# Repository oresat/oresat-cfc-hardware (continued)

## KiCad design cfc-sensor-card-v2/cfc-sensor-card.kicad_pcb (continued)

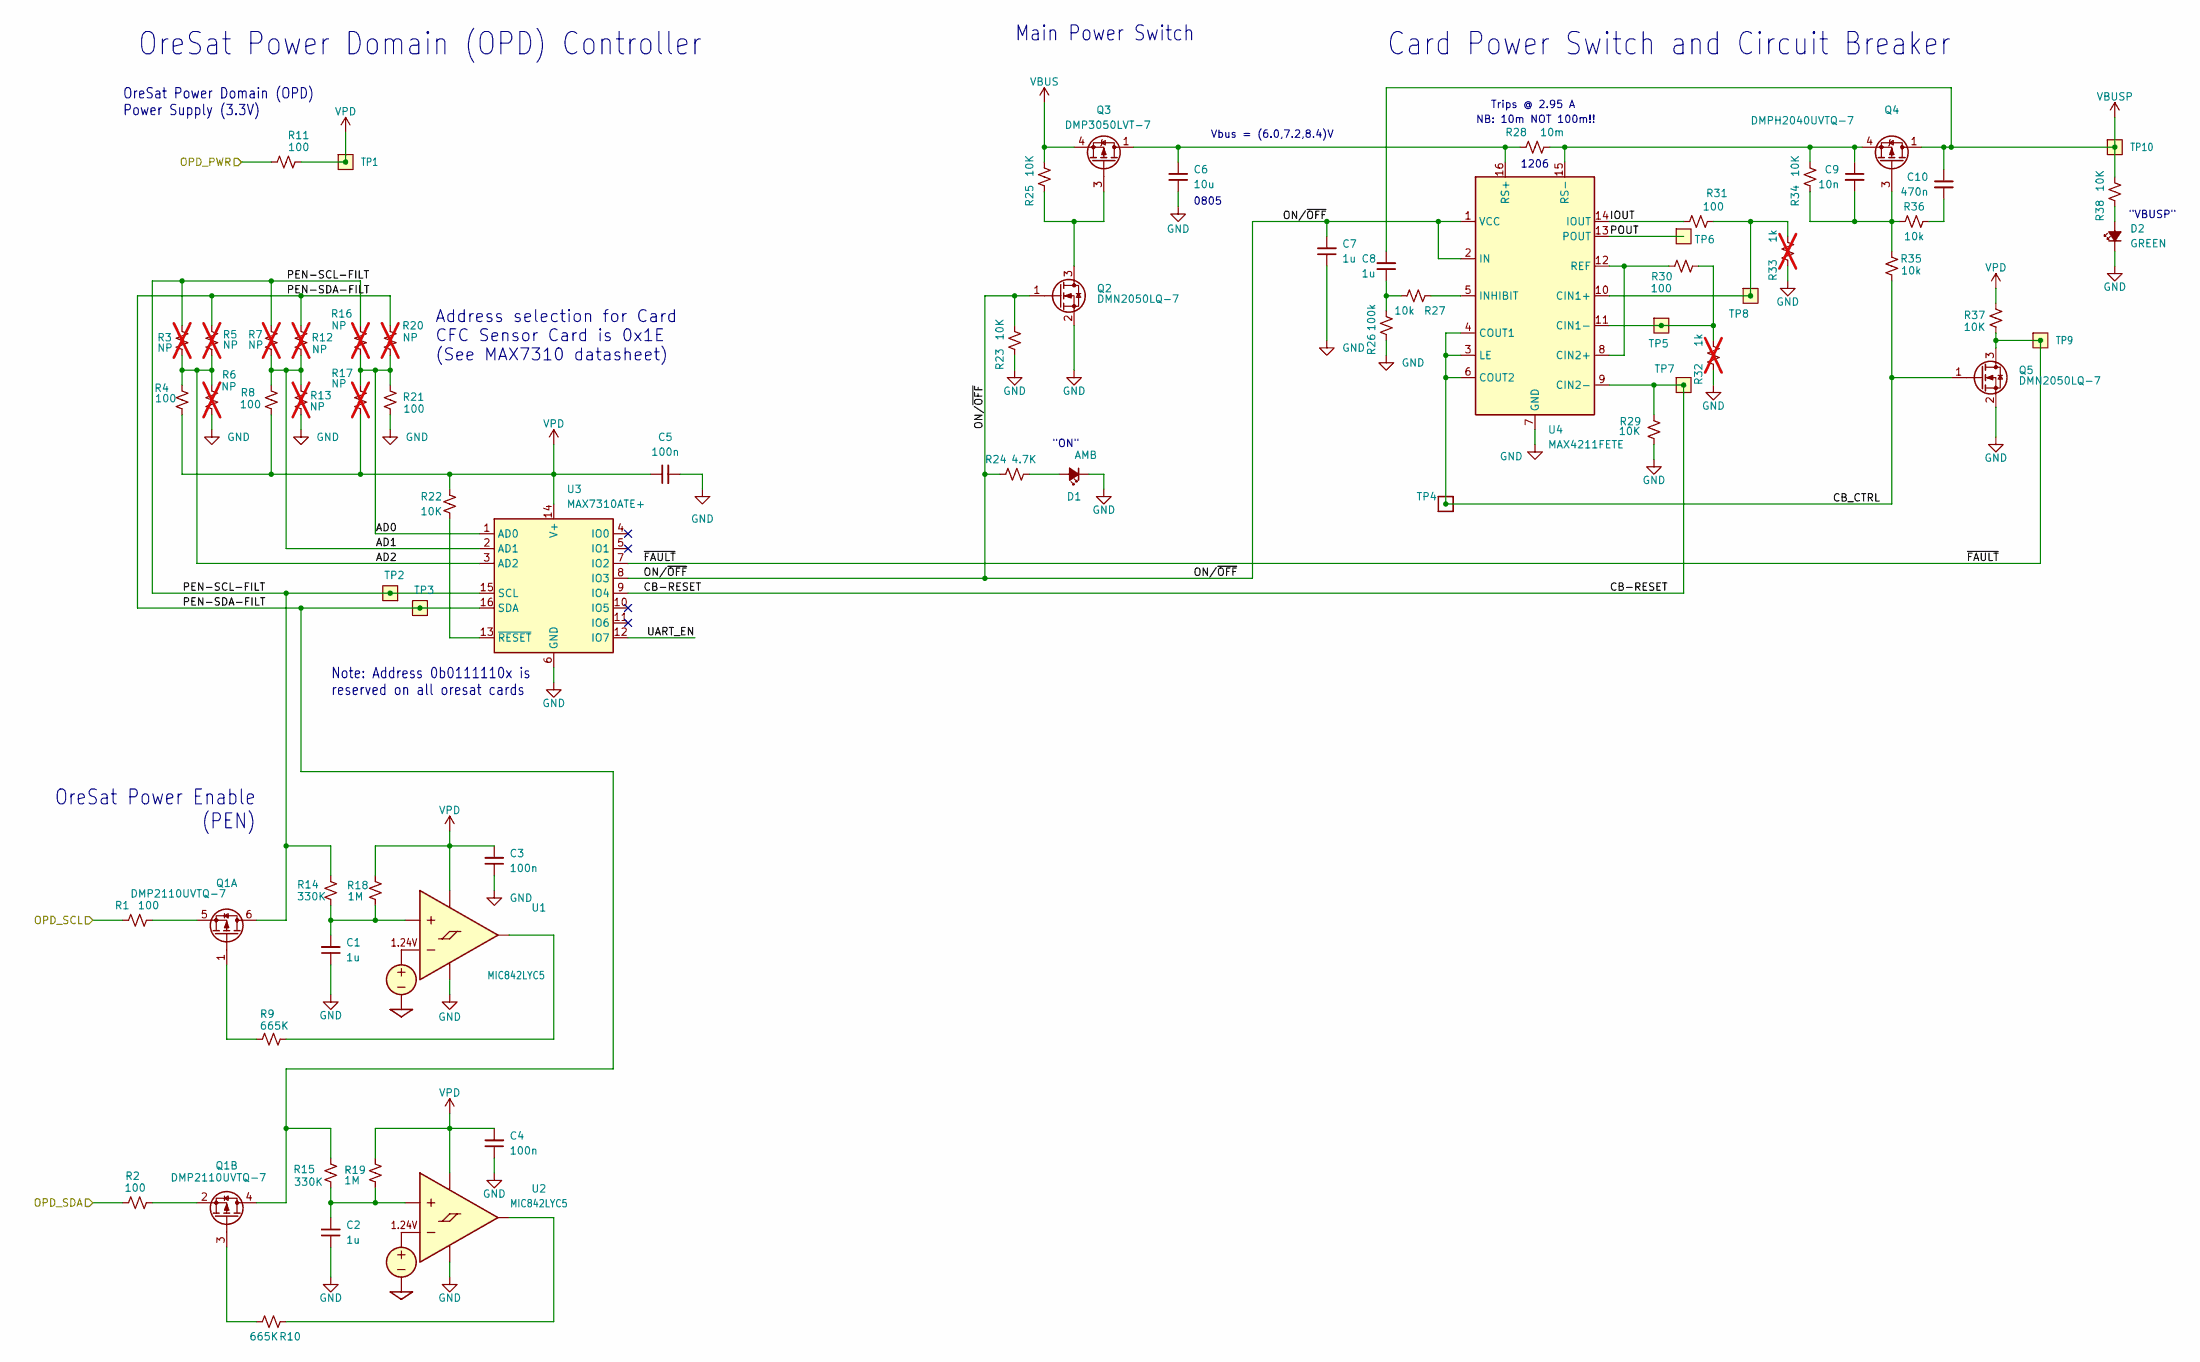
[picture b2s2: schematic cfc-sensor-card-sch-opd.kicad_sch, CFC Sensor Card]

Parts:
C1, C2, C7, C8: 1u; 0603-C-NOSILK; MPN TMK107BJ105KAHT
C3, C4, C5: 100n; 0603-C-NOSILK; MPN TMK107BJ104KAHT
C6: 10u; 0805-C-NOSILK; MPN GRT21BC71E106KE13L
C9: 10n; 0603-C-NOSILK; MPN C0603C103J5RACAUTO
C10: 470n; 0603-C-NOSILK; MPN C0603C474K3RACAUTO
D1: AMB; LED_0603_1608Metric; MPN 150060AS75000
D2: GREEN; LED_0603_1608Metric; MPN 150060GS75000
Q1: DMP2110UVTQ-7; SOT-23-6; MPN DMP2110UVTQ-7
Q2, Q5: DMN2050LQ-7; SOT-23; MPN DMN2050LQ-7
Q3: DMP3050LVT-7; TSOT-23-6; MPN DMP3050LVT-7
Q4: DMPH2040UVTQ-7; TSOT-23-6; MPN DMPH2040UVTQ-7
R1, R2, R4, R8, R11, R21, R30, R31: 100; 0603-C-NOSILK; MPN RMCF0603FT100R
R3, R5, R6, R7, R12, R13, R16, R17, R20: NP; 0603-C-NOSILK; not fitted
R9, R10: 665K; 0603-C-NOSILK; MPN RMCF0603FT665K
R14, R15: 330K; 0603-C-NOSILK; MPN RMCF0603FT330K
R18, R19: 1M; 0603-C-NOSILK; MPN RMCF0603FG1M00
R22, R23, R25, R29, R34, R37, R38: 10K; 0603-C-NOSILK; MPN RMCF0603FT10K0
R24: 4.7K; 0603-C-NOSILK; MPN RMCF0603FT4K70
R26: 100k; 0603-C-NOSILK; MPN RMCF0603FT100K
R27, R35, R36: 10k; 0603-C-NOSILK; MPN RMCF0603FT10K0
R28: 10m; R_1206_3216Metric; MPN CSRF1206FT10L0
R32, R33: 1k; 0603-C-NOSILK; not fitted
TP1, TP9, TP10: Test-Point; TestPoint-0.75mm-th
TP2, TP3, TP5, TP6, TP7, TP8: TEST-POINT; TestPoint-0.75mm-th
TP4: TestPoint-MinTH; TestPoint_Pad_D1.0mm
U1, U2: MIC842LYC5; SOT-353_SC-70-5; MPN MIC842LYC5-TR
U3: MAX7310ATE+; QFN-16-1EP_4x4mm_P0.65mm_EP2.1x2.1mm; MPN MAX7310ATE+
U4: MAX4211FETE; QFN-16-1EP_4x4mm_P0.65mm_EP2.1x2.1mm; MPN MAX4211FETE

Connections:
/OPD/AD0: R16.2, R17.1, R20.2, R21.1, U3.1 (AD0)
/OPD/AD1: R7.2, R8.1, R12.2, R13.1, U3.2 (AD1)
/OPD/AD2: R3.2, R4.1, R5.2, R6.1, U3.3 (AD2)
/OPD/CB-RESET: R29.2, TP7.1 (1_1), U3.9 (IO4), U4.9 (CIN2-)
/OPD/CB_CTRL: Q5.1 (G), R35.2, TP4.1 (1_1), U4.3 (LE), U4.4 (COUT1), U4.6 (COUT2)
/OPD/IOUT: R31.1, U4.14 (IOUT)
/OPD/ON/~OFF: C7.2, Q2.1 (G), R23.2, R24.1, U3.8 (IO3), U4.1 (VCC), U4.2 (IN)
/OPD/OPD_PWR: R11.1; also elsewhere on the board
/OPD/OPD_SCL: R1.1; also elsewhere on the board
/OPD/OPD_SDA: R2.1; also elsewhere on the board
/OPD/PEN-SCL-FILT: Q1.6 (D), R3.1, R7.1, R14.2, R16.1, TP2.1 (1_1), U3.15 (SCL)
/OPD/PEN-SDA-FILT: Q1.4 (D), R5.1, R12.1, R15.2, R20.1, TP3.1 (1_1), U3.16 (SDA)
/OPD/POUT: TP6.1 (1_1), U4.13 (POUT)
/OPD/UART_EN: U3.12 (IO7)
/OPD/~FAULT: Q5.3 (D), R37.1, TP9.1 (1_1), U3.7 (IO2)
unnamed: C8.1, R26.2, R27.2
unnamed: C10.2, R36.2
unnamed: D1.2 (A), R24.2
unnamed: D2.2 (A), R38.1
unnamed: Q1.1 (G), R9.2
unnamed: Q1.5 (S), R1.2
unnamed: Q1.3 (G), R10.2
unnamed: Q1.2 (S), R2.2
unnamed: Q2.3 (D), Q3.3 (G), R25.1
unnamed: C9.2, Q4.3 (G), R34.1, R35.1, R36.1
unnamed: C9.1, Q4.4 (S), R28.2, R34.2, U4.15 (RS-)
unnamed: C1.2, R14.1, R18.1, U1.1 (INP)
unnamed: R9.1, U1.4 (OUT)
unnamed: C2.2, R15.1, R19.1, U2.1 (INP)
unnamed: R10.1, U2.4 (OUT)
unnamed: R22.2, U3.13 (~RESET)
unnamed: R31.2, R33.2, TP8.1 (1_1), U4.10 (CIN1+)
unnamed: R30.2, R32.2, TP5.1 (1_1), U4.11 (CIN1-)
unnamed: R30.1, U4.8 (CIN2+), U4.12 (REF)
unnamed: R27.1, U4.5 (INHIBIT)
unnamed: C6.2, Q3.1 (D), Q3.2 (D), Q3.5 (D), Q3.6 (D), R28.1, U4.16 (RS+)
VBUS: Q3.4 (S), R25.2; also elsewhere on the board
VBUSP: C8.2, C10.1, Q4.1 (D), Q4.2 (D), Q4.5 (D), Q4.6 (D), R38.2, TP10.1 (1_1); also elsewhere on the board
VPD: C3.2, C4.2, C5.1, R4.2, R8.2, R11.2, R17.2, R18.2, R19.2, R22.1, R37.2, TP1.1 (1_1), U1.5 (VDD), U2.5 (VDD), U3.14 (V+)

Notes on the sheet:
Trips @ 2.95 A
Vbus = (6.0,7.2,8.4)V
1206
OreSat Power Domain (OPD) Power Supply (3.3V)
NB: 10m NOT 100m!!
OreSat Power Domain (OPD) Controller
Card Power Switch and Circuit Breaker
Note: Address 0b0111110x is reserved on all oresat cards
"ON"
Address selection for Card CFC Sensor Card is 0x1E (See MAX7310 datasheet)
0805
OreSat Power Enable (PEN)
Main Power Switch
"VBUSP"

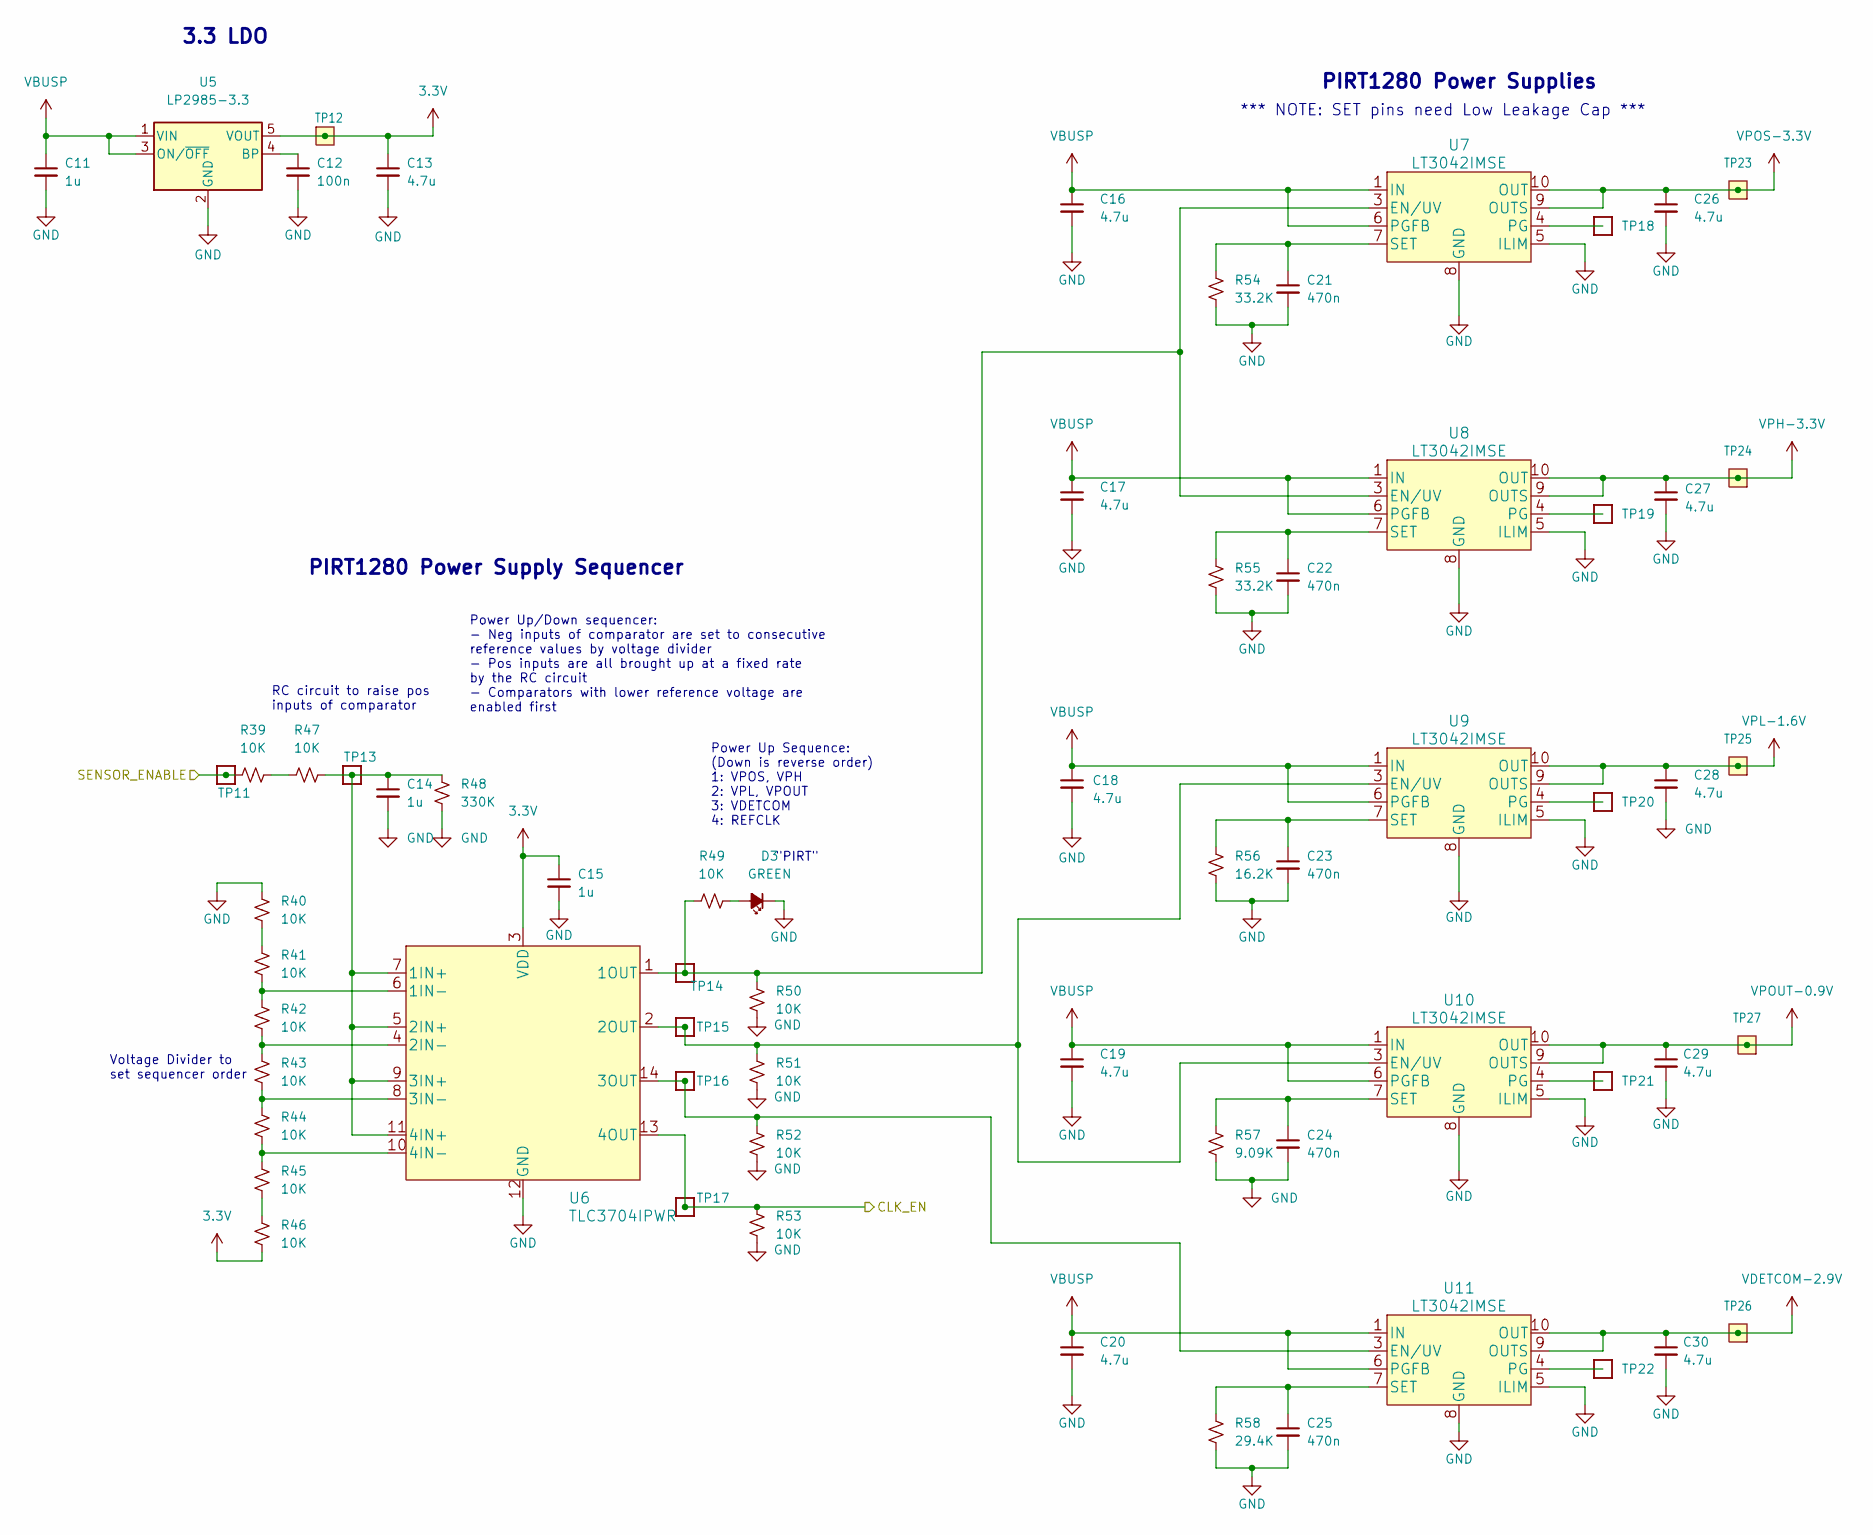
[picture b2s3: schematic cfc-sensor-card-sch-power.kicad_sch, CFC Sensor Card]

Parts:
C11, C14, C15: 1u; 0603-C-NOSILK; MPN TMK107BJ105KAHT
C12: 100n; 0603-C-NOSILK; MPN TMK107BJ104KAHT
C13, C16, C17, C18, C19, C20, C26, C27, C28, C29, C30: 4.7u; 0603-C-NOSILK; MPN EMK107BBJ475KAHT
C21, C22, C23, C24, C25: 470n; 0603-C-NOSILK; MPN C0603C474K3RACAUTO
D3: GREEN; LED_0603_1608Metric; MPN 150060GS75000
R39, R40, R41, R42, R43, R44, R45, R46, R47, R49, R50, R51, R52, R53: 10K; 0603-C-NOSILK; MPN RMCF0603FT10K0
R48: 330K; 0603-C-NOSILK; MPN RMCF0603FT330K
R54, R55: 33.2K; 0603-C-NOSILK; MPN RMCF0603FT33K2
R56: 16.2K; 0603-C-NOSILK; MPN RMCF0603FT16K2
R57: 9.09K; 0603-C-NOSILK; MPN RMCF0603FT9K09
R58: 29.4K; 0603-C-NOSILK; MPN RMCF0603FT29K4
TP11, TP13, TP14, TP15, TP16, TP17, TP18, TP19, TP20, TP21, TP22: TestPoint-MinTH; TestPoint_Pad_D1.0mm
TP12, TP23, TP24, TP25, TP26, TP27: Test-Point; TestPoint-0.75mm-th
U5: LP2985-3.3; SOT-23-5; MPN LP2985AIM5-3.3/NOPB
U6: TLC3704IPWR; TSSOP-14_4.4x5mm_P0.65mm; MPN TLC3704IPWR
U7, U8, U9, U10, U11: LT3042IMSE; MSOP-10-1EP_3x3mm_P0.5mm_EP1.68x1.88mm_0.254_ThermalVias; MPN LT3042IMSE#TRPBF

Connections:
3.3V: C13.1, C15.1, R46.2, TP12.1 (1_1), U5.5 (VOUT), U6.3 (VDD); also elsewhere on the board
/PIRT/CLK_EN: R53.1, TP17.1 (1_1), U6.13 (4OUT); also elsewhere on the board
/SENSOR_ENABLE: R39.1, TP11.1 (1_1); also elsewhere on the board
unnamed: D3.2 (A), R49.2
unnamed: R39.2, R47.1
unnamed: R40.2, R41.1
unnamed: R45.2, R46.1
unnamed: C12.1, U5.4 (BP)
unnamed: C14.1, R47.2, R48.2, TP13.1 (1_1), U6.5 (2IN+), U6.7 (1IN+), U6.9 (3IN+), U6.11 (4IN+)
unnamed: R41.2, R42.1, U6.6 (1IN-)
unnamed: R49.1, R50.1, TP14.1 (1_1), U6.1 (1OUT), U7.3 (EN/UV), U8.3 (EN/UV)
unnamed: R42.2, R43.1, U6.4 (2IN-)
unnamed: R43.2, R44.1, U6.8 (3IN-)
unnamed: R44.2, R45.1, U6.10 (4IN-)
unnamed: TP18.1 (1_1), U7.4 (PG)
unnamed: C21.1, R54.1, U7.7 (SET)
unnamed: TP19.1 (1_1), U8.4 (PG)
unnamed: C22.1, R55.1, U8.7 (SET)
unnamed: TP20.1 (1_1), U9.4 (PG)
unnamed: C23.1, R56.1, U9.7 (SET)
unnamed: R51.1, TP15.1 (1_1), U6.2 (2OUT), U9.3 (EN/UV), U10.3 (EN/UV)
unnamed: TP21.1 (1_1), U10.4 (PG)
unnamed: C24.1, R57.1, U10.7 (SET)
unnamed: R52.1, TP16.1 (1_1), U6.14 (3OUT), U11.3 (EN/UV)
unnamed: TP22.1 (1_1), U11.4 (PG)
unnamed: C25.1, R58.1, U11.7 (SET)
VBUSP: C11.1, C16.1, C17.1, C18.1, C19.1, C20.1, U5.1 (VIN), U5.3 (ON/~OFF), U7.1 (IN), U7.2 (IN), U7.6 (PGFB), U8.1 (IN), U8.2 (IN), U8.6 (PGFB), U9.1 (IN), U9.2 (IN), U9.6 (PGFB), U10.1 (IN), U10.2 (IN), U10.6 (PGFB), U11.1 (IN), U11.2 (IN), U11.6 (PGFB); also elsewhere on the board
VDETCOM-2.9V: C30.1, TP26.1 (1_1), U11.9 (OUTS), U11.10 (OUT); also elsewhere on the board
VPH-3.3V: C27.1, TP24.1 (1_1), U8.9 (OUTS), U8.10 (OUT); also elsewhere on the board
VPL-1.6V: C28.1, TP25.1 (1_1), U9.9 (OUTS), U9.10 (OUT); also elsewhere on the board
VPOS-3.3V: C26.1, TP23.1 (1_1), U7.9 (OUTS), U7.10 (OUT); also elsewhere on the board
VPOUT-0.9V: C29.1, TP27.1 (1_1), U10.9 (OUTS), U10.10 (OUT); also elsewhere on the board

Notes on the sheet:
RC circuit to raise pos inputs of comparator
Voltage Divider to set sequencer order
Power Up/Down sequencer: - Neg inputs of comparator are set to consecutive reference values by voltage divider - Pos inputs are all brought up at a fixed rate by the RC circuit - Comparators with lower reference voltage are enabled first
PIRT1280 Power Supply Sequencer
"PIRT"
*** NOTE: SET pins need Low Leakage Cap ***
Power Up Sequence: (Down is reverse order) 1: ﻿VPOS, VPH 2: VPL, VPOUT 3: VDETCOM 4: REFCLK
3.3 LDO
PIRT1280 Power Supplies

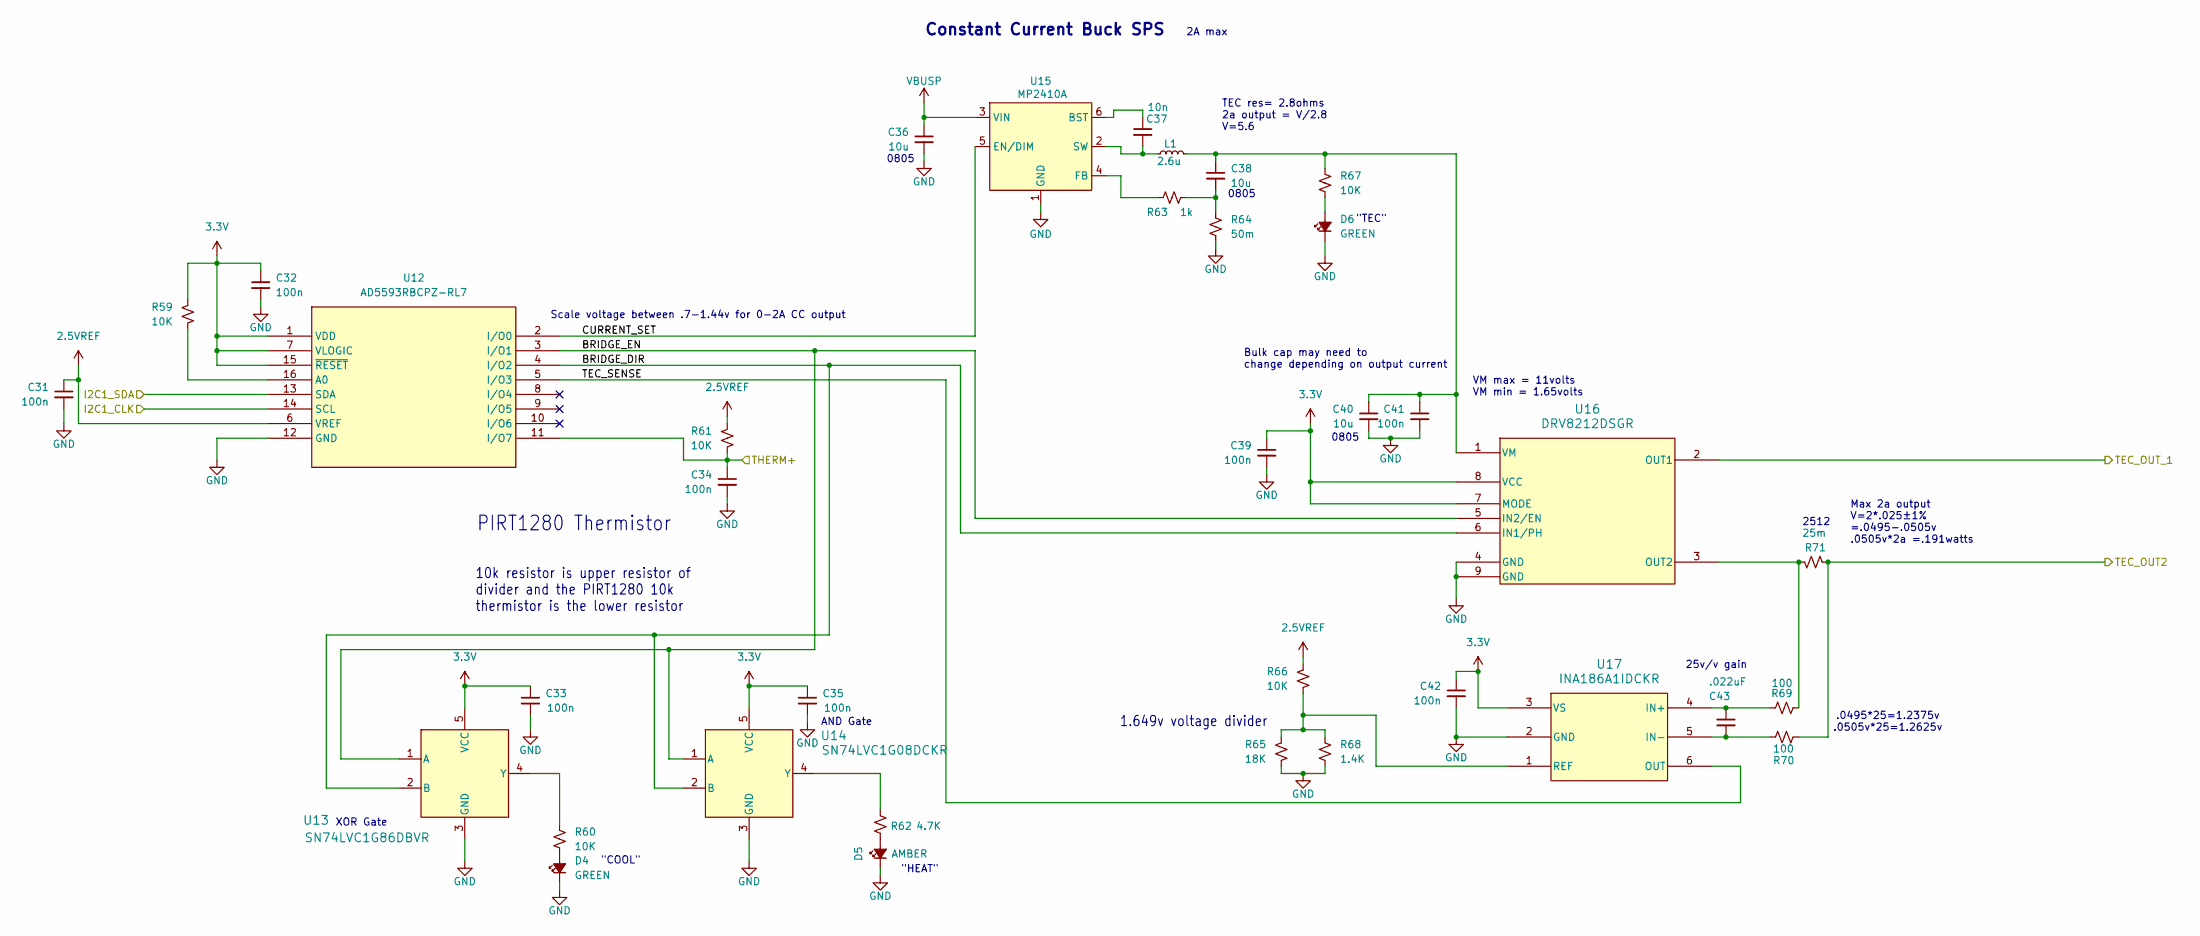
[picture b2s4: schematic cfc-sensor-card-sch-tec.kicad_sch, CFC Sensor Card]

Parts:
C31, C32, C33, C34, C35, C39, C41, C42: 100n; 0603-C-NOSILK; MPN TMK107BJ104KAHT
C36, C38, C40: 10u; 0805-C-NOSILK; MPN GRT21BC71E106KE13L
C37: 10n; 0603-C-NOSILK; MPN KGM15AR71H103KT
C43: .022uF; 0603-C-NOSILK; MPN KAM15AR71H223JT
D4, D6: GREEN; LED_0603_1608Metric; MPN 150060GS75000
D5: AMBER; LED_0603_1608Metric; MPN 150060AS75000
L1: 2.6u; Ind 2.6u 2A; MPN SRR5028-2R6Y
R59, R60, R67: 10K; 0603-C-NOSILK; MPN RMCF0603FT10K0
R61, R66: 10K; 0603-C-NOSILK; MPN RNCF0603TKW10K0
R62: 4.7K; 0603-C-NOSILK; MPN RMCF0603FT4K70
R63: 1k; 0603-C-NOSILK; MPN RMCF0603FT1K00
R64: 50m; 1206-C; MPN KDV12DR050ET
R65: 18K; 0603-C-NOSILK; MPN TNPW060318K0BYCN
R68: 1.4K; 0603-C-NOSILK; MPN RQ73C1J1K4BTD
R69, R70: 100; 0603-C-NOSILK; MPN RMCF0603FT100R
R71: 25m; R_2512_6332Metric; MPN CSNL2512FT25L0
U12: AD5593RBCPZ-RL7; 16-WFQFN, CSP; MPN AD5593RBCPZ-RL7
U13: SN74LVC1G86DBVR; DBV5; MPN SN74LVC1G86DBVR
U14: SN74LVC1G08DCKR; DCK5-L; MPN SN74LVC1G08DCKR
U15: MP2410A; TSOT-23-6; MPN MP2410AGJ-Z
U16: DRV8212DSGR; WSON_212DSGR_TEX; MPN DRV8212DSGR
U17: INA186A1IDCKR; SOIC_IDCKR_TEX; MPN INA186A1IDCKR

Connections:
2.5VREF: C31.1, R61.1, R66.1, U12.6 (VREF)
3.3V: C32.1, C33.1, C35.1, C39.1, C42.1, R59.1, U12.1 (VDD), U12.7 (VLOGIC), U12.15 (~RESET), U13.5 (VCC), U14.5 (VCC), U16.7 (MODE), U16.8 (VCC), U17.3 (VS); also elsewhere on the board
/I2C1_CLK: U12.14 (SCL); also elsewhere on the board
/I2C1_SDA: U12.13 (SDA); also elsewhere on the board
/PIRT/THERM+: C34.1, R61.2, U12.11 (I/O7); also elsewhere on the board
/TEC Control/BRIDGE_DIR: U12.4 (I/O2), U13.2 (B), U14.2 (B), U16.6 (IN1/PH)
/TEC Control/BRIDGE_EN: U12.3 (I/O1), U13.1 (A), U14.1 (A), U16.5 (IN2/EN)
/TEC Control/CURRENT_SET: U12.2 (I/O0), U15.5 (EN/DIM)
/TEC Control/TEC_SENSE: U12.5 (I/O3), U17.6 (OUT)
unnamed: C38.2, R63.2, R64.1
unnamed: D4.2 (A), R60.1
unnamed: D5.2 (A), R62.2
unnamed: D6.2 (A), R67.1
unnamed: R59.2, U12.16 (A0)
unnamed: C37.1, U15.6 (BST)
unnamed: R63.1, U15.4 (FB)
unnamed: C37.2, L1.1, U15.2 (SW)
unnamed: R69.2, R71.1, U16.3 (OUT2)
unnamed: C38.1, C40.1, C41.1, L1.2, R67.2, U16.1 (VM)
unnamed: C43.1, R69.1, U17.4 (IN+)
unnamed: C43.2, R70.1, U17.5 (IN-)
unnamed: R65.1, R66.2, R68.1, U17.1 (REF)
VBUSP: C36.1, U15.3 (VIN); also elsewhere on the board

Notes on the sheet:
0805
2A max
1.649v voltage divider
VM max = 11volts VM min = 1.65volts
XOR Gate
PIRT1280 Thermistor
.0495*25=1.2375v .0505v*25=1.2625v
Scale voltage between .7-1.44v for 0-2A CC output
25v/v gain
TEC res= 2.8ohms 2a output = V/2.8 V=5.6
Constant Current Buck SPS
Bulk cap may need to change depending on output current
"COOL"
"TEC"
"HEAT"
10k resistor is upper resistor of divider and the PIRT1280 10k thermistor is the lower resistor
2512
Max 2a output V=2*.025±1% =.0495-.0505v .0505v*2a =.191watts
AND Gate

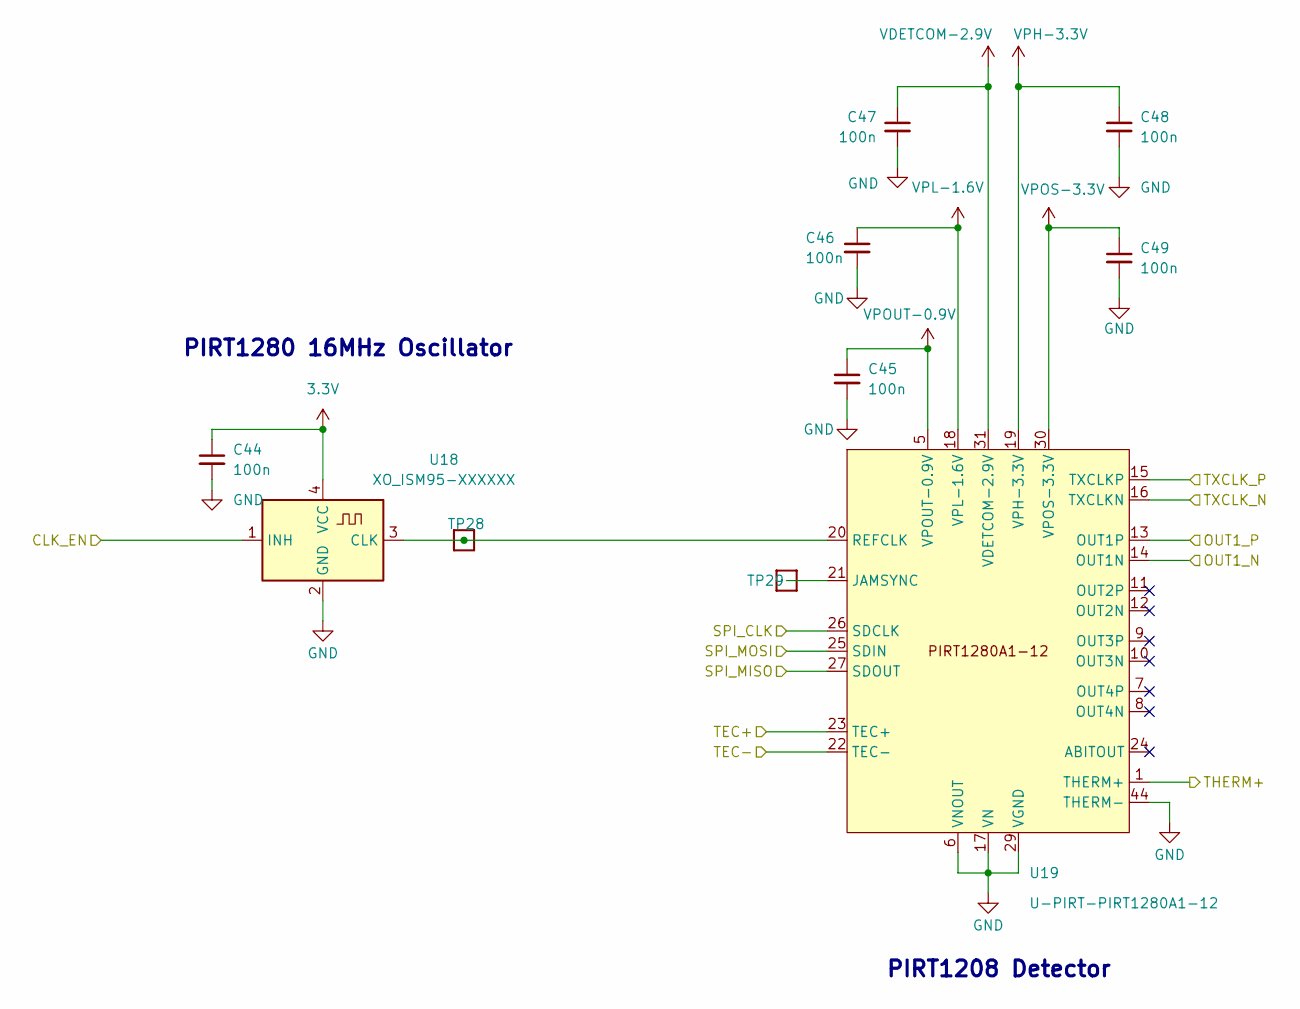
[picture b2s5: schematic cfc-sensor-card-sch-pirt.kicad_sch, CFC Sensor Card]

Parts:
C44, C45, C46, C47, C48, C49: 100n; 0603-C-NOSILK; MPN TMK107BJ104KAHT
TP28, TP29: TestPoint-MinTH; TestPoint_Pad_D1.0mm
U18: XO_ISM95-XXXXXX; MPN ISM95-3251AH-16.000MHZ
U19: U-PIRT-PIRT1280A1-12; PIRT1280A1-12; MPN PIRT1280A1-12

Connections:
3.3V: C44.1, U18.4 (VCC); also elsewhere on the board
/OUT1_N: U19.14 (OUT1N); also elsewhere on the board
/OUT1_P: U19.13 (OUT1P); also elsewhere on the board
/PIRT/CLK_EN: U18.1 (INH); also elsewhere on the board
/PIRT/THERM+: U19.1 (THERM+); also elsewhere on the board
/SPI_CLK: U19.26 (SDCLK); also elsewhere on the board
/SPI_MISO: U19.27 (SDOUT); also elsewhere on the board
/SPI_MOSI: U19.25 (SDIN); also elsewhere on the board
/TXCLK_N: U19.16 (TXCLKN); also elsewhere on the board
/TXCLK_P: U19.15 (TXCLKP); also elsewhere on the board
unnamed: TP28.1 (1_1), U18.3 (CLK), U19.20 (REFCLK)
unnamed: TP29.1 (1_1), U19.21 (JAMSYNC)
VDETCOM-2.9V: C47.1, U19.31 (VDETCOM-2.9V); also elsewhere on the board
VPH-3.3V: C48.1, U19.19 (VPH-3.3V); also elsewhere on the board
VPL-1.6V: C46.1, U19.18 (VPL-1.6V); also elsewhere on the board
VPOS-3.3V: C49.1, U19.30 (VPOS-3.3V); also elsewhere on the board
VPOUT-0.9V: C45.1, U19.5 (VPOUT-0.9V); also elsewhere on the board

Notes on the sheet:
PIRT1280 16MHz Oscillator
PIRT1208 Detector

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
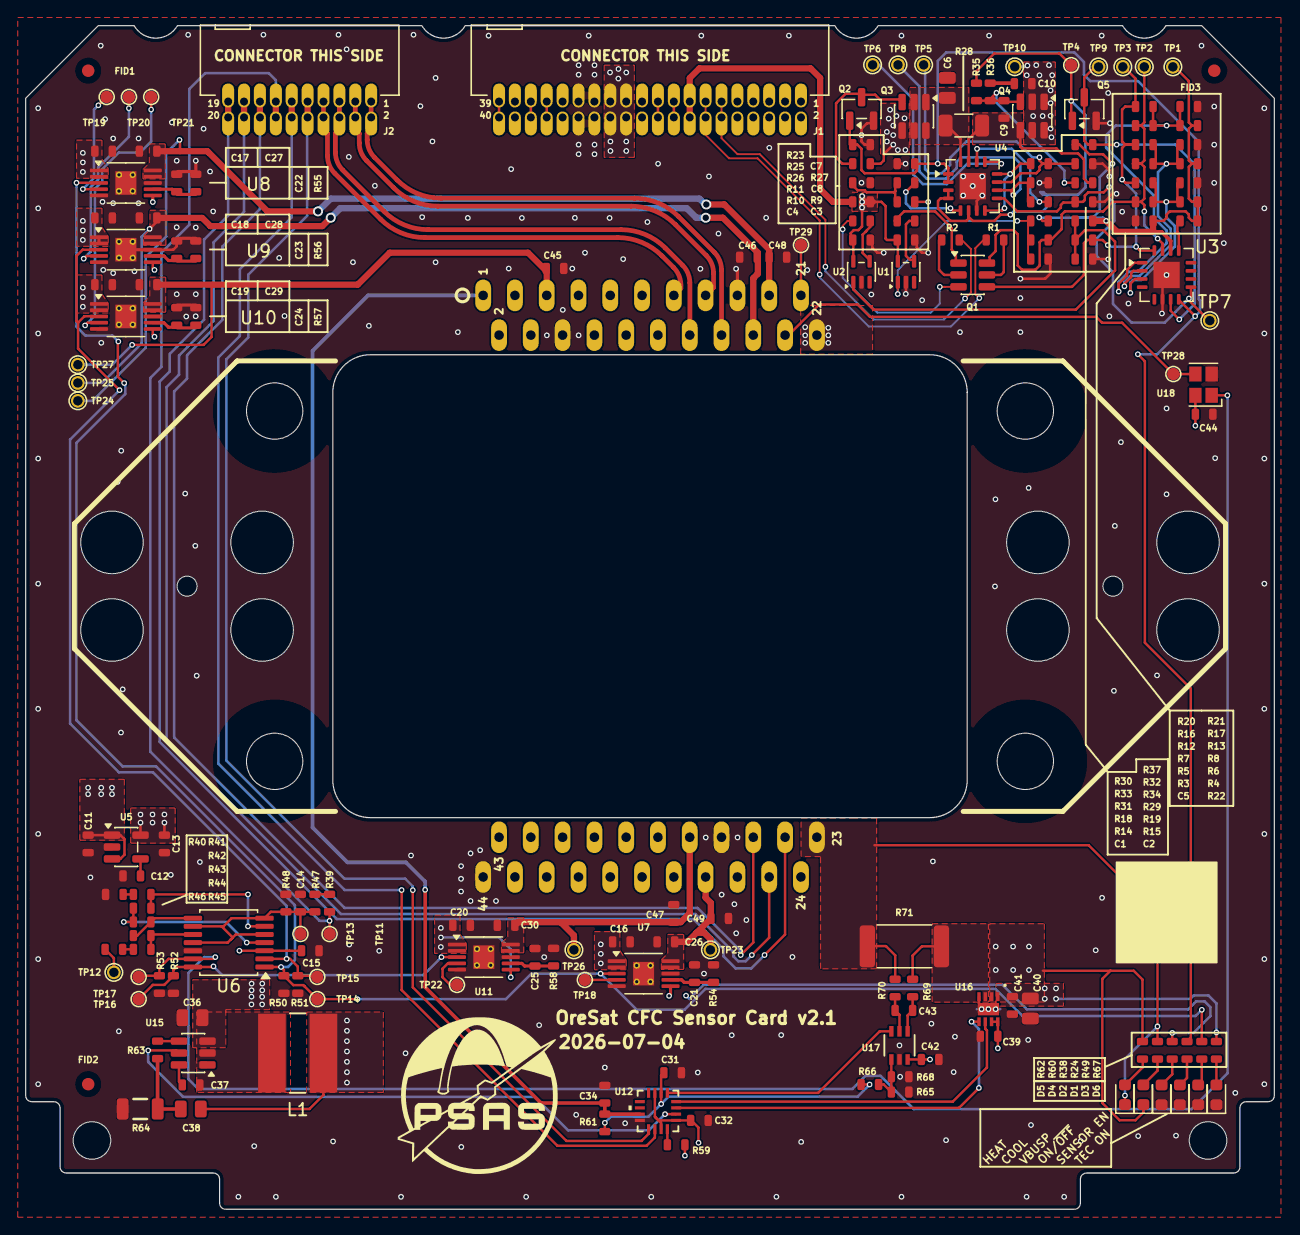
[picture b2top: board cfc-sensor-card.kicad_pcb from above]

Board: 4 copper layers, 99.8 x 94.6 mm, 182 parts (1 on the bottom side), 107 nets.

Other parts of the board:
PCB1: ORESAT-CARD-V1.3-CFC-SENSOR-V1.0

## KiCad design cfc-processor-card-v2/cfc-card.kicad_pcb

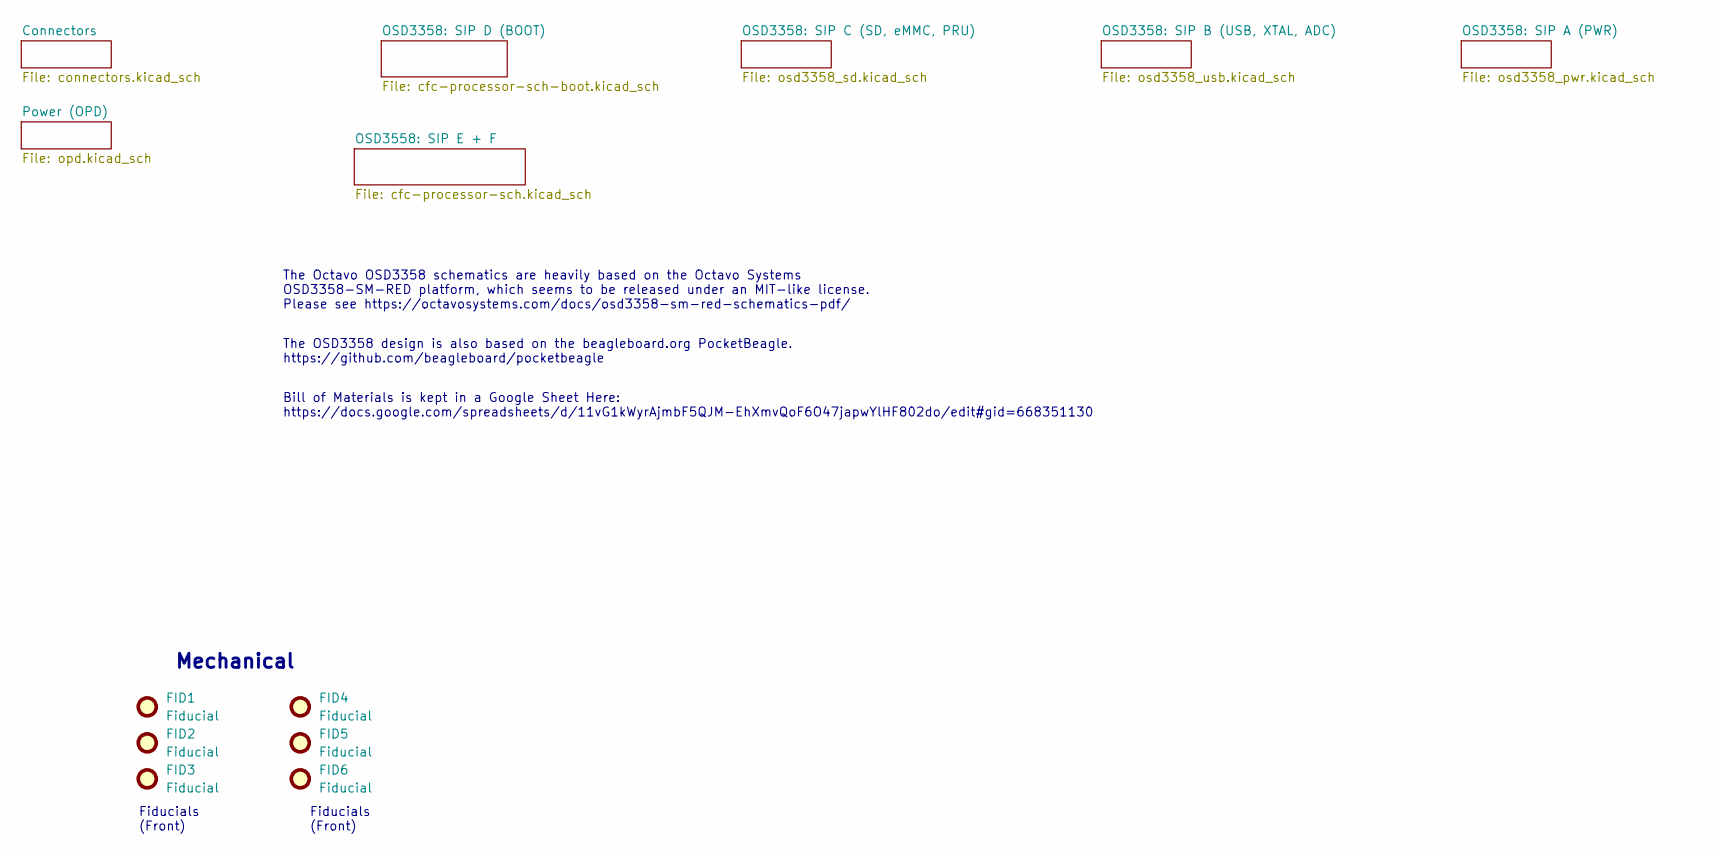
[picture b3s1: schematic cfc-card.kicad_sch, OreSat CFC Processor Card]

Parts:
FID1, FID2, FID3, FID4, FID5, FID6: Fiducial; Fiducial_1mm_Mask2mm

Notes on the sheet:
Bill of Materials is kept in a Google Sheet Here: https://docs.google.com/spreadsheets/d/11vG1kWyrAjmbF5QJM-EhXmvQoF6O47japwYlHF802do/edit#gid=668351130
The OSD3358 design is also based on the beagleboard.org PocketBeagle. https://github.com/beagleboard/pocketbeagle
Mechanical
Fiducials (Front)
The Octavo OSD3358 schematics are heavily based on the Octavo Systems OSD3358-SM-RED platform, which seems to be released under an MIT-like license. Please see https://octavosystems.com/docs/osd3358-sm-red-schematics-pdf/

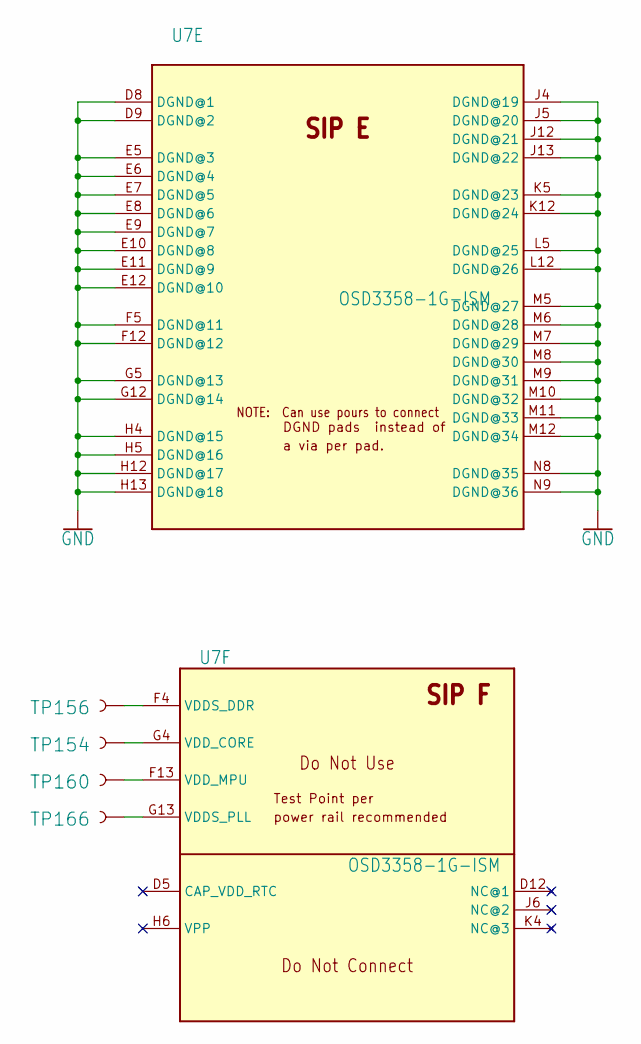
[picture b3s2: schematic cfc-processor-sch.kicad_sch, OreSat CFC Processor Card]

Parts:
TP154, TP156, TP160, TP166: TEST-POINT3X4; PAD.03X.04
U7: OSD3358-1G-ISM; U-Octavo-OSD335X-BGA-256; MPN OSD3358-1G-ISM

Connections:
GND: U7.D8 (DGND@1), U7.D9 (DGND@2), U7.E5 (DGND@3), U7.E6 (DGND@4), U7.E7 (DGND@5), U7.E8 (DGND@6), U7.E9 (DGND@7), U7.E10 (DGND@8), U7.E11 (DGND@9), U7.E12 (DGND@10), U7.F5 (DGND@11), U7.F12 (DGND@12), U7.G5 (DGND@13), U7.G12 (DGND@14), U7.H4 (DGND@15), U7.H5 (DGND@16), U7.H12 (DGND@17), U7.H13 (DGND@18), U7.J4 (DGND@19), U7.J5 (DGND@20), U7.J12 (DGND@21), U7.J13 (DGND@22), U7.K5 (DGND@23), U7.K12 (DGND@24), U7.L5 (DGND@25), U7.L12 (DGND@26), U7.M5 (DGND@27), U7.M6 (DGND@28), U7.M7 (DGND@29), U7.M8 (DGND@30), U7.M9 (DGND@31), U7.M10 (DGND@32), U7.M11 (DGND@33), U7.M12 (DGND@34), U7.N8 (DGND@35), U7.N9 (DGND@36); also elsewhere on the board
unnamed: TP154.P$1 (1), U7.G4 (VDD_CORE)
unnamed: TP156.P$1 (1), U7.F4 (VDDS_DDR)
unnamed: TP160.P$1 (1), U7.F13 (VDD_MPU)
unnamed: TP166.P$1 (1), U7.G13 (VDDS_PLL)
